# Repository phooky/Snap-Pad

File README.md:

Snap-Pad provides an easy, somewhat safe two party one time pad capability.

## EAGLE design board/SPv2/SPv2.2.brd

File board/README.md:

These are the Eagle CAD board files and libraries for the Snap-Pad.
The files in this directory are published under the CERN Open Hardware License.
See the file "cern_ohl_v_1_2.txt" in the parent directory for more information.

The libraries are in the "lbr" directory; the schematics and boards are in the "Snap-Pad" directory.

SP.sch is the schematic for one-half of a Snap-Pad.
SP.brd is the board file for one-half of a Snap-Pad.
SP-twin.brd is the full board file for the twinned Snap-Pad. There is no associated
  schematic; forward/back annotation is severed and the components are cloned to
  avoid any messiness with part naming. It's a symmetrical board.

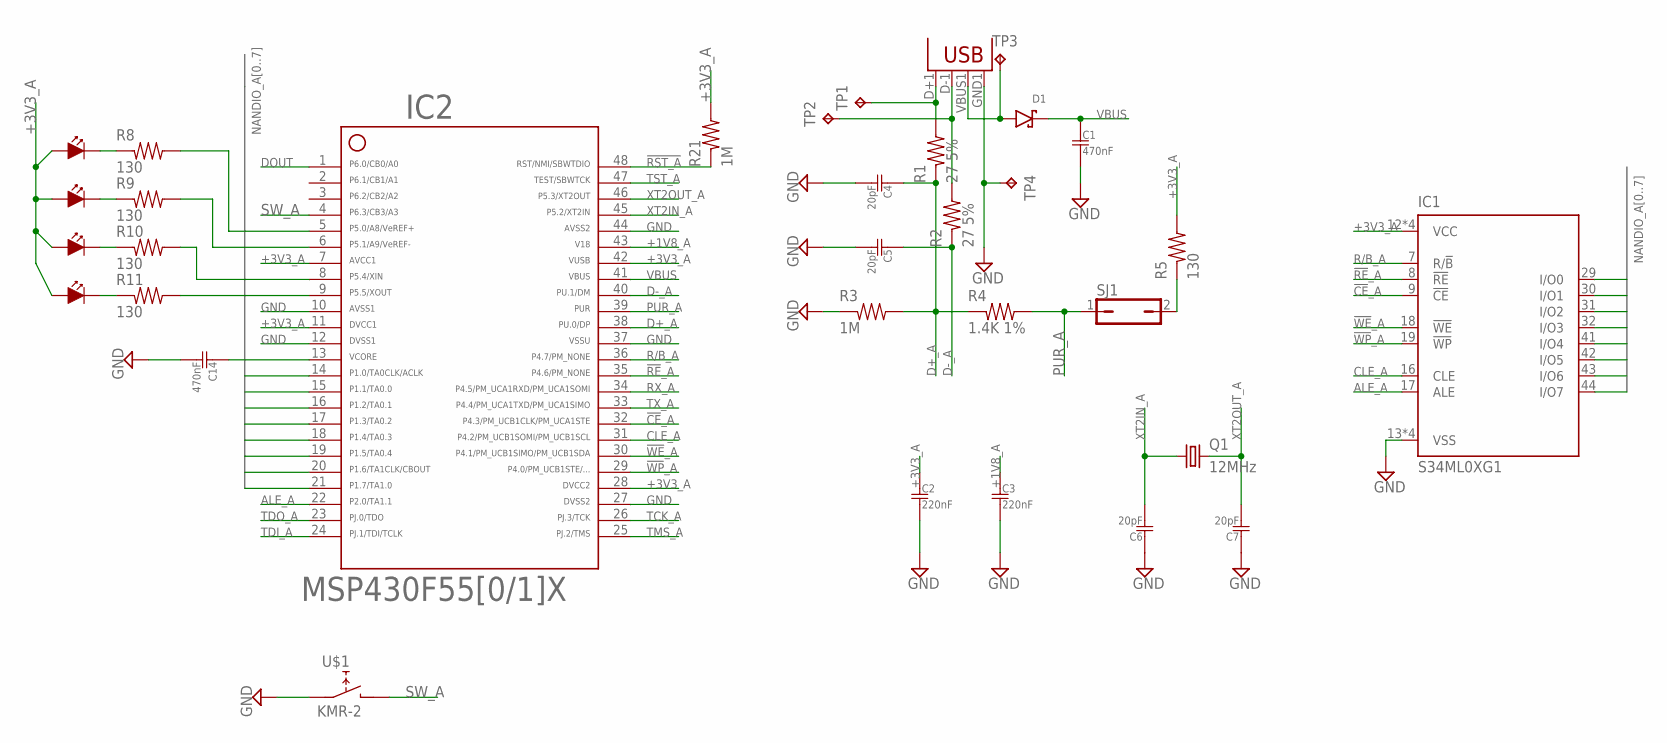
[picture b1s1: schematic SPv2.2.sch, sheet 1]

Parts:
C1, C14: 470nF; R0805
C2, C3: 220nF; R0805
C4, C5, C6, C7: 20pF; R0805
D1: D-SCHOTTKY; SOD123
IC1: S34ML0XG1; TSOP48
IC2: F5508; PT48
JP1: USBA-SMD-MALE; USB-A-SMT-MALE
Q1: 12MHz; CSM-3X
R1, R2: 27 5%; R0805
R3, R21: 1M; R0805
R4: 1.4K 1%; R0805
R5, R8, R9, R10, R11: 130; R0805
SJ1: JP1Q; JP1
TP1, TP2, TP3, TP4: TPTP13R; TP13R
U$1: KMR-2; KMR-2-SWITCH
U$5, U$6, U$7, U$8: LED; LED0805

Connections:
!CE!_A: IC1.9 (!CE), IC2.32
!RE!_A: IC1.8 (!RE), IC2.35
!RST_A!: IC2.48, R21.P$1 (1)
!WE!_A: IC1.18 (!WE), IC2.30
!WP!_A: IC1.19 (!WP), IC2.29
+1V8_A: C3.P$1 (1), IC2.43
+3V3_A: C2.P$1 (1), IC1.12 (VCC), IC1.34 (VCC), IC1.37 (VCC), IC1.39 (VCC), IC2.7, IC2.11, IC2.28, IC2.42, R5.P$2 (2), R21.P$2 (2), U$5.ANODE, U$6.ANODE, U$7.ANODE, U$8.ANODE
ALE_A: IC1.17 (ALE), IC2.22
CLE_A: IC1.16 (CLE), IC2.31
D+_A: C4.P$1 (1), IC2.38, R1.P$1 (1), R3.P$2 (2), R4.P$1 (1)
D-_A: C5.P$1 (1), IC2.40, R2.P$1 (1)
DOUT: IC2.1; also elsewhere on the board
GND: C1.P$2 (2), C2.P$2 (2), C3.P$2 (2), C4.P$2 (2), C5.P$2 (2), C6.P$1 (1), C7.P$1 (1), C14.P$2 (2), IC1.13 (VSS), IC1.25 (VSS), IC1.36 (VSS), IC1.48 (VSS), IC2.10, IC2.12, IC2.27, IC2.37, IC2.44, JP1.GND1 (GND), R3.P$1 (1), TP4.TP, U$1.PA1 (A1), U$1.PA2 (A1); also elsewhere on the board
unnamed: JP1.D+1 (D+), R1.P$2 (2), TP1.TP
unnamed: JP1.D-1 (D-), R2.P$2 (2), TP2.TP
unnamed: C14.P$1 (1), IC2.13
unnamed: R5.P$1 (1), SJ1.2
unnamed: IC2.9, R11.P$2 (2)
unnamed: R10.P$1 (1), U$7.CATHODE
unnamed: R9.P$1 (1), U$6.CATHODE
unnamed: R8.P$1 (1), U$5.CATHODE
unnamed: R11.P$1 (1), U$8.CATHODE
unnamed: IC2.8, R10.P$2 (2)
unnamed: IC2.6, R9.P$2 (2)
unnamed: IC2.5, R8.P$2 (2)
unnamed: D1.ANODE, JP1.VBUS1 (VBUS), TP3.TP
NANDIO_A0: IC1.29 (I/O0), IC2.14
NANDIO_A1: IC1.30 (I/O1), IC2.15
NANDIO_A2: IC1.31 (I/O2), IC2.16
NANDIO_A3: IC1.32 (I/O3), IC2.17
NANDIO_A4: IC1.41 (I/O4), IC2.18
NANDIO_A5: IC1.42 (I/O5), IC2.19
NANDIO_A6: IC1.43 (I/O6), IC2.20
NANDIO_A7: IC1.44 (I/O7), IC2.21
PUR_A: IC2.39, R4.P$2 (2), SJ1.1
R/B_A: IC1.7 (R/!B), IC2.36
RX_A: IC2.34; also elsewhere on the board
SW_A: IC2.4, U$1.PB1 (B), U$1.PB2 (B)
TCK_A: IC2.26
TDI_A: IC2.24
TDO_A: IC2.23
TMS_A: IC2.25
TST_A: IC2.47
TX_A: IC2.33; also elsewhere on the board
VBUS: C1.P$1 (1), D1.CATHODE, IC2.41; also elsewhere on the board
XT2IN_A: C6.P$2 (2), IC2.45, Q1.P$1 (1)
XT2OUT_A: C7.P$2 (2), IC2.46, Q1.P$2 (2)

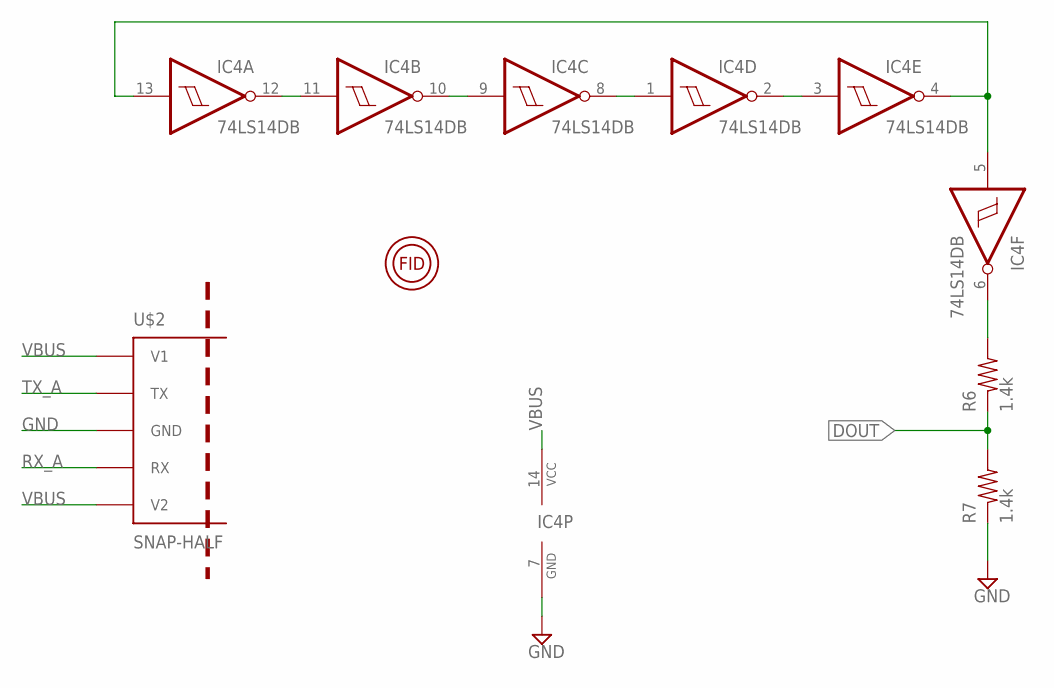
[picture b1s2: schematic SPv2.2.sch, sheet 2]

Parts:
IC4: 74LS14DB; SSOP14
R6, R7: 1.4k; R0805
U$2: SNAP-HALF
U$3: FIDUCAL

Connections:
DOUT: R6.P$1 (1), R7.P$2 (2); also elsewhere on the board
GND: IC4.7 (GND), R7.P$1 (1), U$2.P$3 (GND); also elsewhere on the board
unnamed: IC4.11 (I), IC4.12 (O)
unnamed: IC4.9 (I), IC4.10 (O)
unnamed: IC4.1 (I), IC4.8 (O)
unnamed: IC4.2 (O), IC4.3 (I)
unnamed: IC4.4 (O), IC4.5 (I), IC4.13 (I)
unnamed: IC4.6 (O), R6.P$2 (2)
RX_A: U$2.P$4 (RX); also elsewhere on the board
TX_A: U$2.P$2 (TX); also elsewhere on the board
VBUS: IC4.14 (VCC), U$2.P$1 (V1), U$2.P$5 (V2); also elsewhere on the board

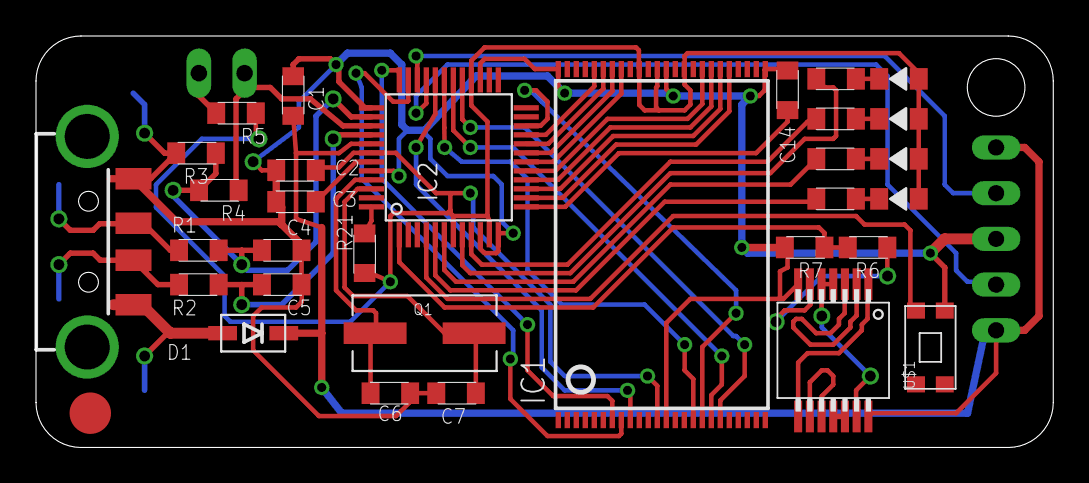
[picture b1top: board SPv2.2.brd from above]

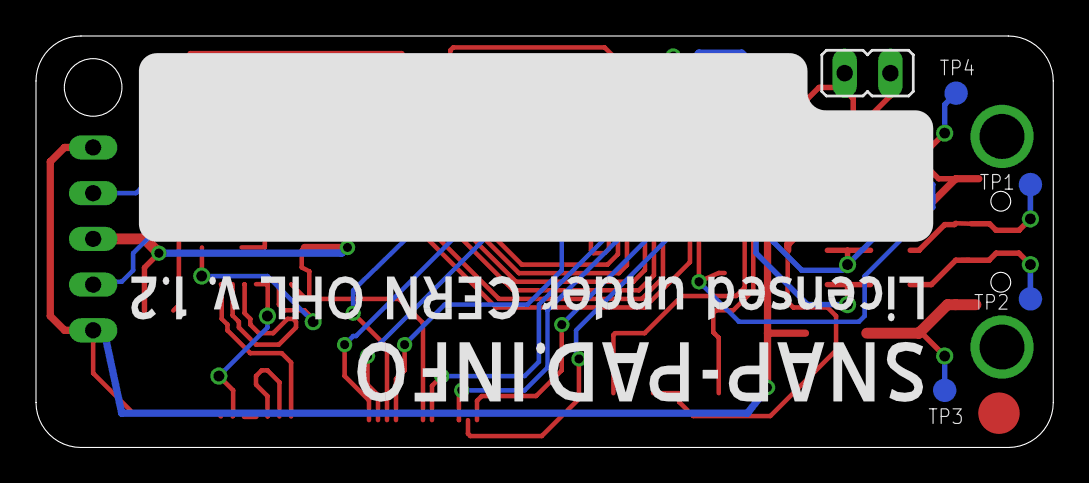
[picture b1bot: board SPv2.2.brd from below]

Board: 2 copper layers, 56.5 x 22.9 mm, 38 parts (6 on the bottom side), 48 nets.

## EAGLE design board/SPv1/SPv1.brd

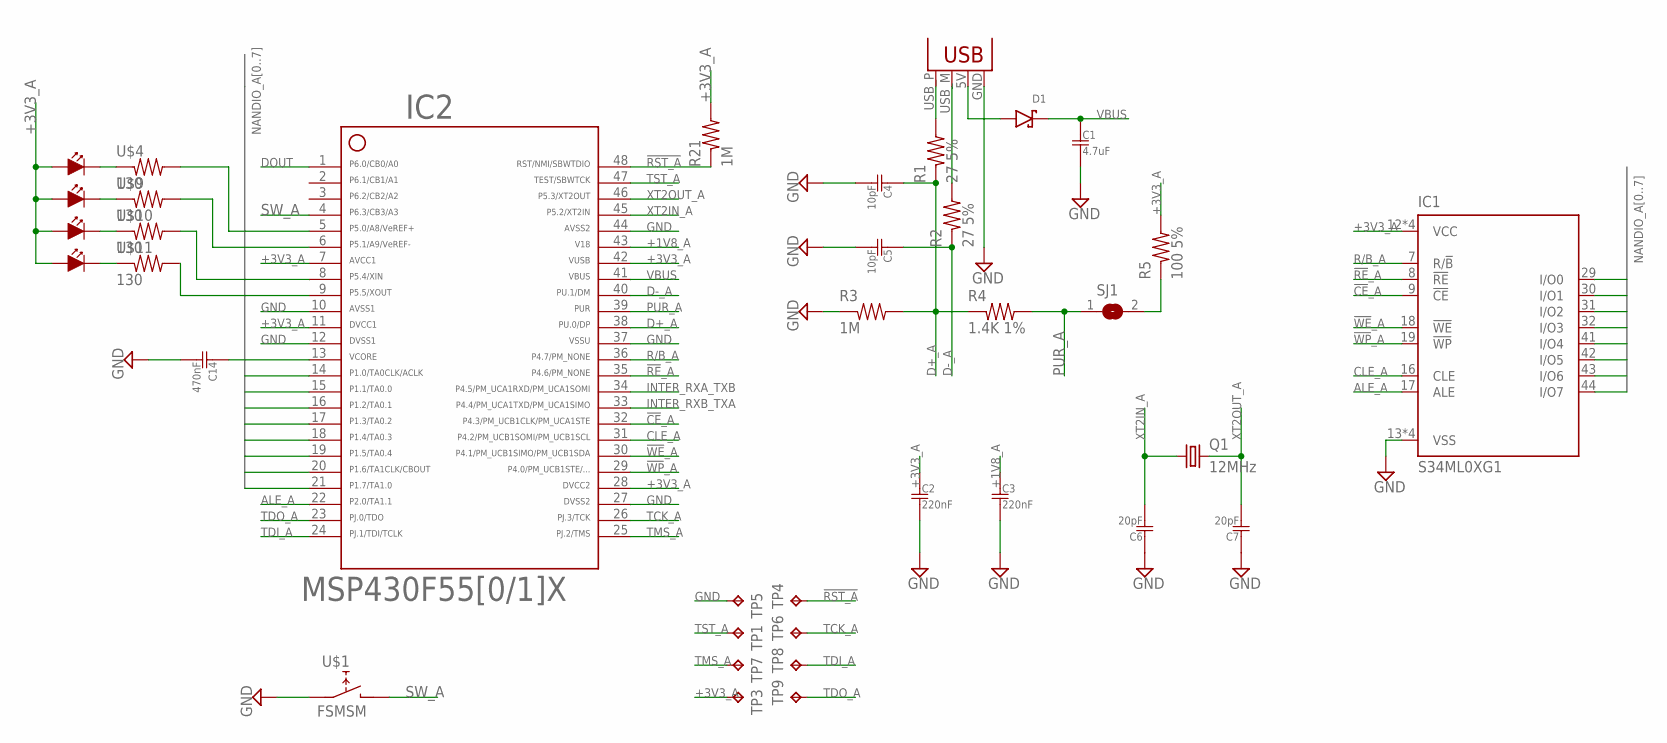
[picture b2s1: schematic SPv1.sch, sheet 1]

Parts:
C1: 4.7uF; R0805
C2, C3: 220nF; R0805
C4, C5: 10pF; R0805
C6, C7: 20pF; R0805
C14: 470nF; R0805
D1: D-SCHOTTKY; SOD123
IC1: S34ML0XG1; TSOP48
IC2: F55[0/1]X---PT48; PT48
JP1: USBPCB; USB-A-PCB
Q1: 12MHz; CSM-3X
R1, R2: 27 5%; R0805
R3, R21: 1M; R0805
R4: 1.4K 1%; R0805
R5: 100 5%; R0805
SJ1: SJW
TP1, TP3, TP4, TP5, TP6, TP7, TP8, TP9: TPTP08SQ; TP08SQ
U$1: FSMSM
U$4, U$9, U$10, U$11: 130; R0805
U$5, U$6, U$7, U$8: LED; LED0805

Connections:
!CE!_A: IC1.9 (!CE), IC2.32
!RE!_A: IC1.8 (!RE), IC2.35
!RST_A!: IC2.48, R21.P$1 (1), TP4.TP
!WE!_A: IC1.18 (!WE), IC2.30
!WP!_A: IC1.19 (!WP), IC2.29
+1V8_A: C3.P$1 (1), IC2.43
+3V3_A: C2.P$1 (1), IC1.12 (VCC), IC1.34 (VCC), IC1.37 (VCC), IC1.39 (VCC), IC2.7, IC2.11, IC2.28, IC2.42, R5.P$2 (2), R21.P$2 (2), TP3.TP, U$5.ANODE, U$6.ANODE, U$7.ANODE, U$8.ANODE
ALE_A: IC1.17 (ALE), IC2.22
CLE_A: IC1.16 (CLE), IC2.31
D+_A: C4.P$1 (1), IC2.38, R1.P$1 (1), R3.P$2 (2), R4.P$1 (1)
D-_A: C5.P$1 (1), IC2.40, R2.P$1 (1)
DOUT: IC2.1; also elsewhere on the board
GND: C1.P$2 (2), C2.P$2 (2), C3.P$2 (2), C4.P$2 (2), C5.P$2 (2), C6.P$1 (1), C7.P$1 (1), C14.P$2 (2), IC1.13 (VSS), IC1.25 (VSS), IC1.36 (VSS), IC1.48 (VSS), IC2.10, IC2.12, IC2.27, IC2.37, IC2.44, JP1.GND, R3.P$1 (1), TP5.TP, U$1.P$1 (A1); also elsewhere on the board
INTER_RXA_TXB: IC2.34; also elsewhere on the board
INTER_RXB_TXA: IC2.33; also elsewhere on the board
unnamed: JP1.USB_P (D+), R1.P$2 (2)
unnamed: JP1.USB_M (D-), R2.P$2 (2)
unnamed: C14.P$1 (1), IC2.13
unnamed: R5.P$1 (1), SJ1.2
unnamed: IC2.9, U$11.P$2 (2)
unnamed: U$7.CATHODE, U$10.P$1 (1)
unnamed: U$6.CATHODE, U$9.P$1 (1)
unnamed: U$4.P$1 (1), U$5.CATHODE
unnamed: U$8.CATHODE, U$11.P$1 (1)
unnamed: IC2.8, U$10.P$2 (2)
unnamed: IC2.6, U$9.P$2 (2)
unnamed: IC2.5, U$4.P$2 (2)
unnamed: D1.ANODE, JP1.5V (VBUS)
NANDIO_A0: IC1.29 (I/O0), IC2.14
NANDIO_A1: IC1.30 (I/O1), IC2.15
NANDIO_A2: IC1.31 (I/O2), IC2.16
NANDIO_A3: IC1.32 (I/O3), IC2.17
NANDIO_A4: IC1.41 (I/O4), IC2.18
NANDIO_A5: IC1.42 (I/O5), IC2.19
NANDIO_A6: IC1.43 (I/O6), IC2.20
NANDIO_A7: IC1.44 (I/O7), IC2.21
PUR_A: IC2.39, R4.P$2 (2), SJ1.1
R/B_A: IC1.7 (R/!B), IC2.36
SW_A: IC2.4, U$1.P$2 (B)
TCK_A: IC2.26, TP6.TP
TDI_A: IC2.24, TP8.TP
TDO_A: IC2.23, TP9.TP
TMS_A: IC2.25, TP7.TP
TST_A: IC2.47, TP1.TP
VBUS: C1.P$1 (1), D1.CATHODE, IC2.41; also elsewhere on the board
XT2IN_A: C6.P$2 (2), IC2.45, Q1.P$1 (1)
XT2OUT_A: C7.P$2 (2), IC2.46, Q1.P$2 (2)

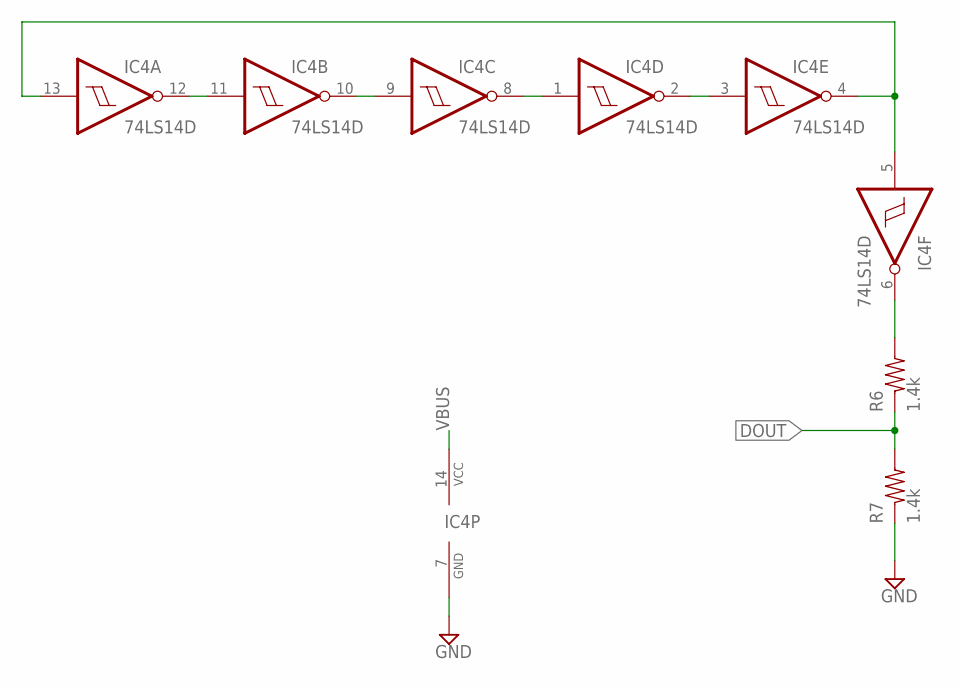
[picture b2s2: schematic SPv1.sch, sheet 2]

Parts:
IC4: 74LS14D; SO14
R6, R7: 1.4k; R0805

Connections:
DOUT: R6.P$1 (1), R7.P$2 (2); also elsewhere on the board
GND: IC4.7 (GND), R7.P$1 (1); also elsewhere on the board
unnamed: IC4.11 (I), IC4.12 (O)
unnamed: IC4.9 (I), IC4.10 (O)
unnamed: IC4.1 (I), IC4.8 (O)
unnamed: IC4.2 (O), IC4.3 (I)
unnamed: IC4.4 (O), IC4.5 (I), IC4.13 (I)
unnamed: IC4.6 (O), R6.P$2 (2)
VBUS: IC4.14 (VCC); also elsewhere on the board

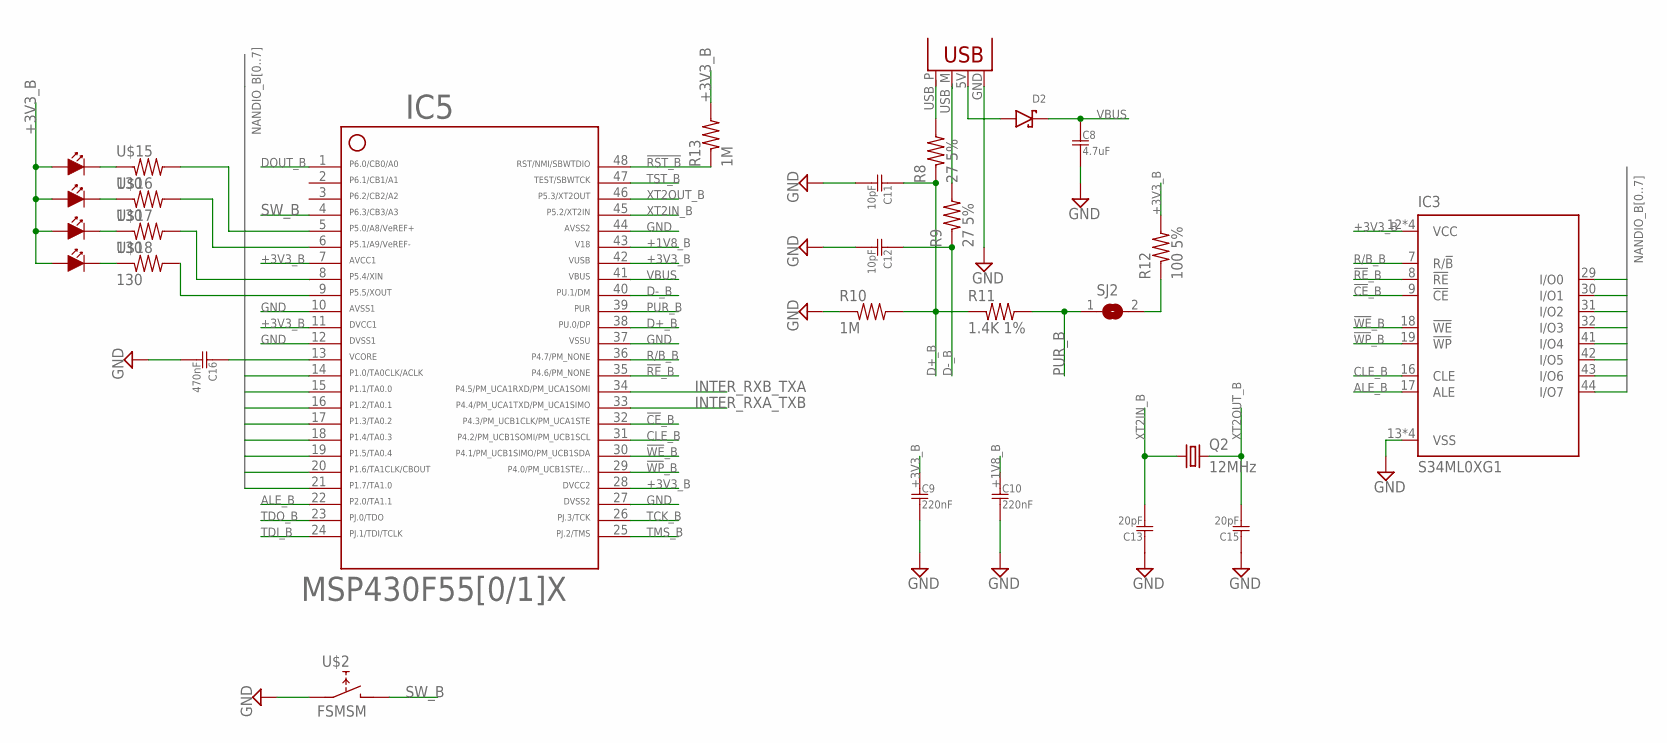
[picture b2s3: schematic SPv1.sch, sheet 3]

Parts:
C8: 4.7uF; R0805
C9, C10: 220nF; R0805
C11, C12: 10pF; R0805
C13, C15: 20pF; R0805
C16: 470nF; R0805
D2: D-SCHOTTKY; SOD123
IC3: S34ML0XG1; TSOP48
IC5: F55[0/1]X---PT48; PT48
JP2: USBPCB; USB-A-PCB
Q2: 12MHz; CSM-3X
R8, R9: 27 5%; R0805
R10, R13: 1M; R0805
R11: 1.4K 1%; R0805
R12: 100 5%; R0805
SJ2: SJW
U$2: FSMSM
U$3, U$12, U$13, U$14: LED; LED0805
U$15, U$16, U$17, U$18: 130; R0805

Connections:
!CE!_B: IC3.9 (!CE), IC5.32
!RE!_B: IC3.8 (!RE), IC5.35
!RST_B!: IC5.48, R13.P$1 (1)
!WE!_B: IC3.18 (!WE), IC5.30
!WP!_B: IC3.19 (!WP), IC5.29
+1V8_B: C10.P$1 (1), IC5.43
+3V3_B: C9.P$1 (1), IC3.12 (VCC), IC3.34 (VCC), IC3.37 (VCC), IC3.39 (VCC), IC5.7, IC5.11, IC5.28, IC5.42, R12.P$2 (2), R13.P$2 (2), U$3.ANODE, U$12.ANODE, U$13.ANODE, U$14.ANODE
ALE_B: IC3.17 (ALE), IC5.22
CLE_B: IC3.16 (CLE), IC5.31
D+_B: C11.P$1 (1), IC5.38, R8.P$1 (1), R10.P$2 (2), R11.P$1 (1)
D-_B: C12.P$1 (1), IC5.40, R9.P$1 (1)
DOUT_B: IC5.1; also elsewhere on the board
GND: C8.P$2 (2), C9.P$2 (2), C10.P$2 (2), C11.P$2 (2), C12.P$2 (2), C13.P$1 (1), C15.P$1 (1), C16.P$2 (2), IC3.13 (VSS), IC3.25 (VSS), IC3.36 (VSS), IC3.48 (VSS), IC5.10, IC5.12, IC5.27, IC5.37, IC5.44, JP2.GND, R10.P$1 (1), U$2.P$1 (A1); also elsewhere on the board
INTER_RXA_TXB: IC5.33; also elsewhere on the board
INTER_RXB_TXA: IC5.34; also elsewhere on the board
unnamed: JP2.USB_P (D+), R8.P$2 (2)
unnamed: JP2.USB_M (D-), R9.P$2 (2)
unnamed: C16.P$1 (1), IC5.13
unnamed: U$13.CATHODE, U$17.P$1 (1)
unnamed: U$12.CATHODE, U$16.P$1 (1)
unnamed: U$3.CATHODE, U$15.P$1 (1)
unnamed: U$14.CATHODE, U$18.P$1 (1)
unnamed: IC5.9, U$18.P$2 (2)
unnamed: IC5.8, U$17.P$2 (2)
unnamed: IC5.6, U$16.P$2 (2)
unnamed: IC5.5, U$15.P$2 (2)
unnamed: R12.P$1 (1), SJ2.2
unnamed: D2.ANODE, JP2.5V (VBUS)
NANDIO_A8: IC3.29 (I/O0), IC5.14
NANDIO_A9: IC3.30 (I/O1), IC5.15
NANDIO_A10: IC3.31 (I/O2), IC5.16
NANDIO_A11: IC3.32 (I/O3), IC5.17
NANDIO_A12: IC3.41 (I/O4), IC5.18
NANDIO_A13: IC3.42 (I/O5), IC5.19
NANDIO_A14: IC3.43 (I/O6), IC5.20
NANDIO_A15: IC3.44 (I/O7), IC5.21
PUR_B: IC5.39, R11.P$2 (2), SJ2.1
R/B_B: IC3.7 (R/!B), IC5.36
SW_B: IC5.4, U$2.P$2 (B)
TCK_B: IC5.26
TDI_B: IC5.24
TDO_B: IC5.23
TMS_B: IC5.25
TST_B: IC5.47
VBUS: C8.P$1 (1), D2.CATHODE, IC5.41; also elsewhere on the board
XT2IN_B: C13.P$2 (2), IC5.45, Q2.P$1 (1)
XT2OUT_B: C15.P$2 (2), IC5.46, Q2.P$2 (2)

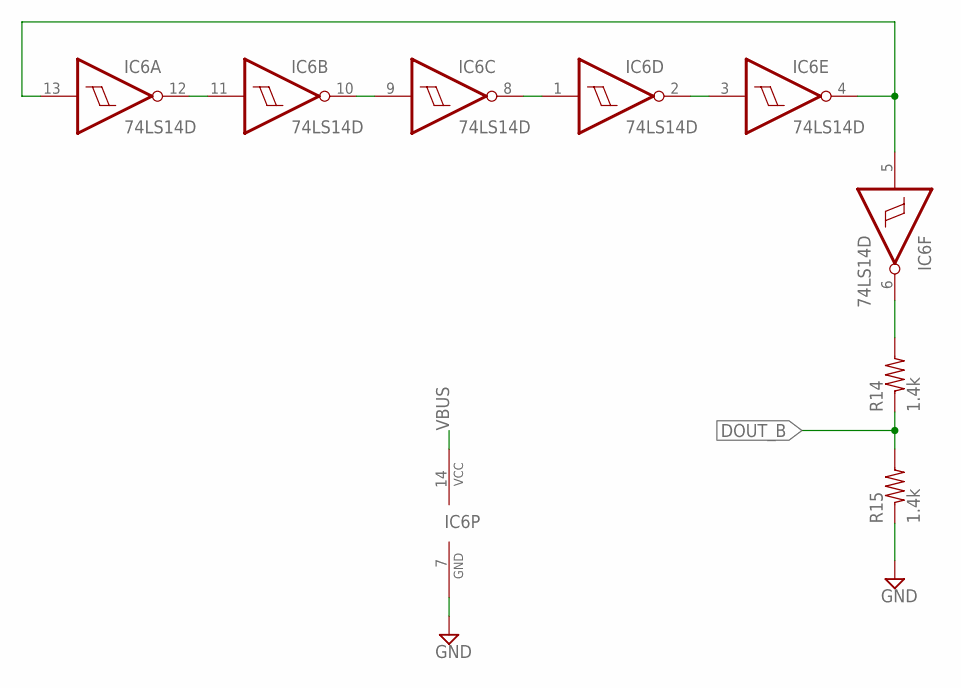
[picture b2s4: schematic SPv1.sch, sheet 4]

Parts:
IC6: 74LS14D; SO14
R14, R15: 1.4k; R0805

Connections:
DOUT_B: R14.P$1 (1), R15.P$2 (2); also elsewhere on the board
GND: IC6.7 (GND), R15.P$1 (1); also elsewhere on the board
unnamed: IC6.11 (I), IC6.12 (O)
unnamed: IC6.9 (I), IC6.10 (O)
unnamed: IC6.1 (I), IC6.8 (O)
unnamed: IC6.2 (O), IC6.3 (I)
unnamed: IC6.4 (O), IC6.5 (I), IC6.13 (I)
unnamed: IC6.6 (O), R14.P$2 (2)
VBUS: IC6.14 (VCC); also elsewhere on the board

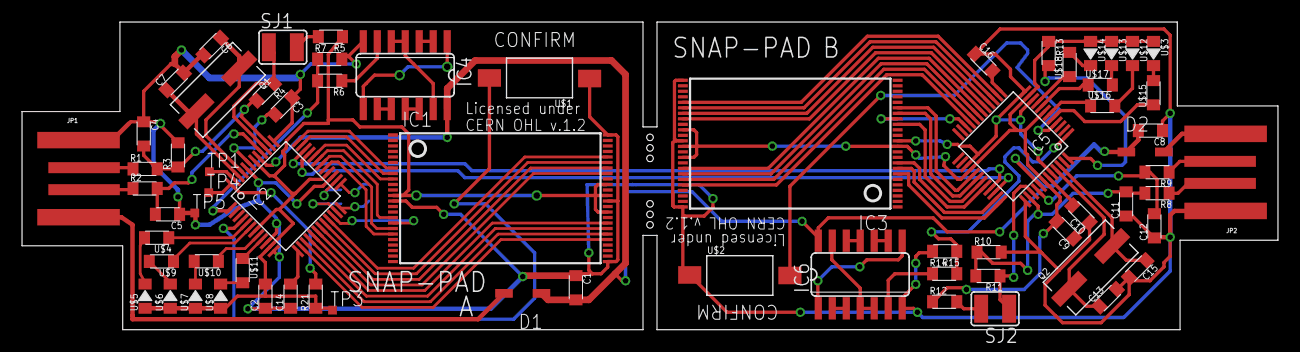
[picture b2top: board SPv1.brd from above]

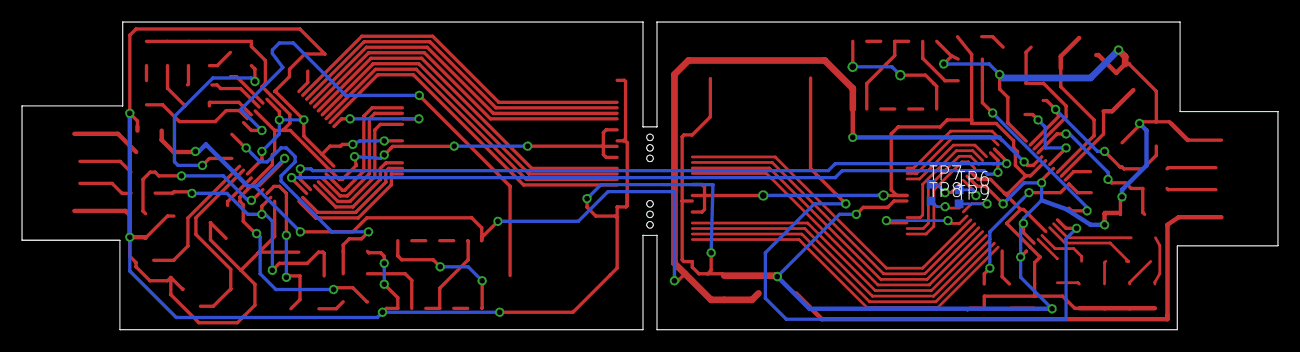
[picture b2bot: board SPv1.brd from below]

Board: 2 copper layers, 114.0 x 27.9 mm, 72 parts (4 on the bottom side), 97 nets.

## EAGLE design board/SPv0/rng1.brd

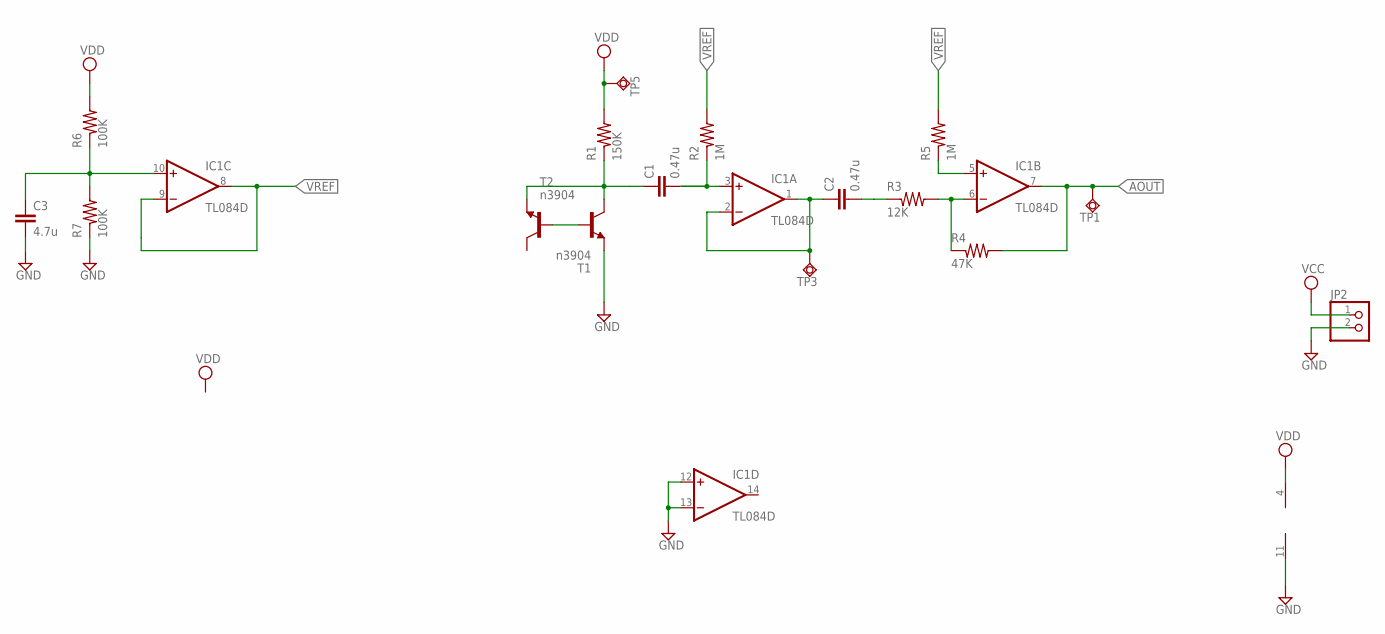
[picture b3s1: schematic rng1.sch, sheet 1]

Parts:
C1, C2: 0.47u; C0805
C3: 4.7u; C0805
IC1: TL084D; SO14
JP2: PINHD-1X2; 1X02
R1: 150K; R0805
R2, R5: 1M; R0805
R3: 12K; R0805
R4: 47K; R0805
R6, R7: 100K; R0805
T1, T2: n3904; SOT23-BEC
TP1, TP3, TP5: TPSQPAD1-13; P1-13

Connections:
AOUT: IC1.7 (OUT), R4.P$2 (2), TP1.TP
GND: C3.2, IC1.11 (V-), IC1.12 (+IN), IC1.13 (-IN), JP2.2, R7.P$1 (1), T2.E; also elsewhere on the board
unnamed: C1.1, R1.P$1 (1), T1.E, T2.C
unnamed: C3.1, IC1.10 (+IN), R6.P$1 (1), R7.P$2 (2)
unnamed: T1.B, T2.B
unnamed: C1.2, IC1.3 (+IN), R2.P$1 (1)
unnamed: C2.1, IC1.1 (OUT), IC1.2 (-IN), TP3.TP
unnamed: C2.2, R3.P$1 (1)
unnamed: IC1.6 (-IN), R3.P$2 (2), R4.P$1 (1)
unnamed: IC1.5 (+IN), R5.P$1 (1)
VCC: JP2.1; also elsewhere on the board
VDD: IC1.4 (V+), R1.P$2 (2), R6.P$2 (2), TP5.TP; also elsewhere on the board
VREF: IC1.8 (OUT), IC1.9 (-IN), R2.P$2 (2), R5.P$2 (2)

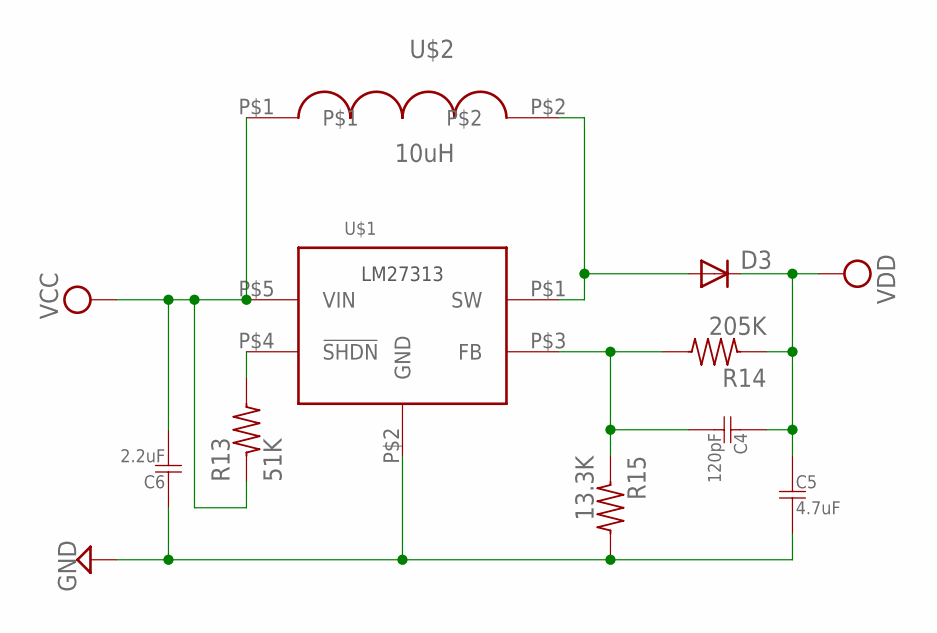
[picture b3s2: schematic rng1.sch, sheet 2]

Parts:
C4: 120pF; R0805
C5: 4.7uF; R0805
C6: 2.2uF; R0805
D3: DIODE-SOD123; SOD123
R13: 51K; R0805
R14: 205K; R0805
R15: 13.3K; R0805
U$1: LM27313; SOT-23-5
U$2: 10uH; L1007

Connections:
GND: C5.P$2 (2), C6.P$1 (1), R15.P$2 (2), U$1.P$2 (GND); also elsewhere on the board
unnamed: R13.P$2 (2), U$1.P$4 (!SHDN!)
unnamed: D3.A, U$1.P$1 (SW), U$2.P$2
unnamed: C4.P$2 (2), R14.P$2 (2), R15.P$1 (1), U$1.P$3 (FB)
VCC: C6.P$2 (2), R13.P$1 (1), U$1.P$5 (VIN), U$2.P$1; also elsewhere on the board
VDD: C4.P$1 (1), C5.P$1 (1), D3.C, R14.P$1 (1); also elsewhere on the board

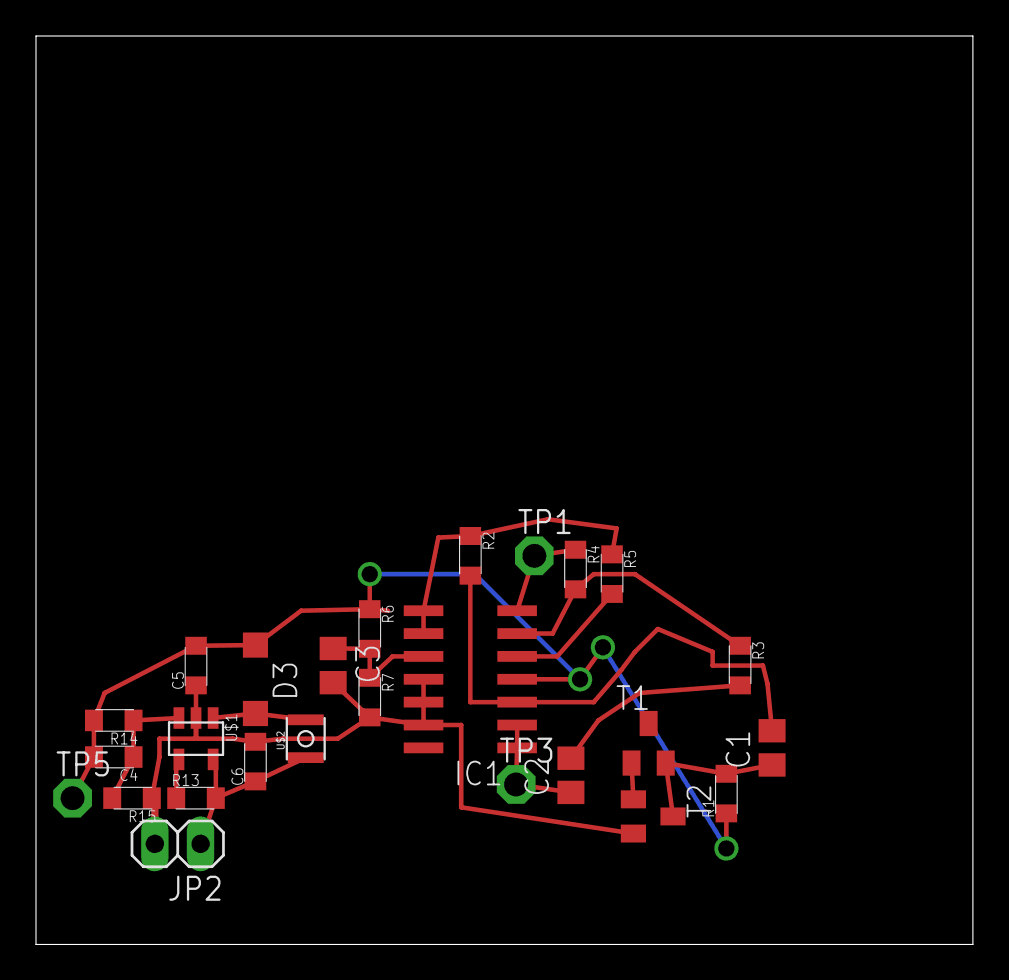
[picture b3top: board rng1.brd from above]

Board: 2 copper layers, 52.0 x 50.5 mm, 26 parts (0 on the bottom side), 16 nets.

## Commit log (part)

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2013-10-26 adding datasheets, flash lib, and schematic start
2013-10-26 adding readme with basic todo and scheduling
2013-10-26 doc for msp430f5508 (x53x was the wrong chip)
2013-10-26 readding hardware user guide
2013-10-26 superceded document
2013-10-27 added uC, xtal, decoupling caps for uC, usb lines/power
2013-10-28 added crystal footprint; added to schematic
2013-10-29 adding RNG ideas
2013-10-29 Added nets and busses for NAND/MSP430 interconnect Designated some pins for RNG
2013-11-23 adding rough circuit for random number generator based on avalanche noise
2013-11-23 reducing to original circuit
2013-11-25 removed obvious ERC problems
2013-11-26 layout of rng in good shape
2013-11-26 pre-autoroute
2013-12-16 fixup usb problems
2013-12-19 adding in descriptors for usb
2013-12-19 adding CCS project for snap-pad v0
2013-12-19 Set most pins to inputs Never stop screaming
2013-12-20 ONFI verified
2013-12-20 rough implementation of raw page read/program
2013-12-21 adding very simple interactivity over cdc
2013-12-23 wait for ready line on reads
2013-12-23 added block erase
2013-12-24 adding documentation
2013-12-24 added own footprints for 0805 parts reorganizing board somewhat
2013-12-26 added LEDs, starting layout
2013-12-26 added schottky diode to library fixed up led symbol swapping in sod123 diode for d1
2013-12-31 fxing up library parts added prototype for read parameter page
2014-01-01 parameter page read command tested
2014-01-01 add doc
2014-01-05 expose raw nand flash read
2014-01-05 adding hooks for experimentation
2014-01-05 pipe XT2 to ACLK pin (should have div 0)
2014-01-06 huh. sending the ACLK signal out on P1.0 makes nand access unreliable. Will have to recheck schematic.
2014-01-06 port already opened by constructor
2014-01-06 adding adc-based hwrng
2014-01-07 adding ADC rng code for shits and giggles
2014-01-07 adding some additional doc
2014-01-08 halfboard v1 done!
2014-01-10 added v1 board with snapping action
2014-01-16 better handling for multiple commands in succession; lib for nand hacking, added some more tests
2014-01-16 adding script for mapping bad blocks
2014-01-18 adding one time pad chip code
2014-01-20 adding header parsing/writing
2014-01-24 fixes to board (connector; PUR line)
2014-01-24 adding extended hamming SEC-DED coding as well as tests
2014-01-24 added CERN OHL notice and moved confirm text to tNames
2014-01-24 add current version of nand code; lint ecc.c
2014-01-24 cleaning up board slightly and prepping for double-sided placement on v2
2014-01-25 toward header initialization
2014-01-26 first pass at header initialization code
2014-01-27 adding main
2014-01-28 close to working initialization; some problem with next_good; writing tons of paragraphs
2014-01-28 header initialization working
2014-01-28 adding switch support
2014-01-28 recognize when SP is not in primary mode.
2014-02-11 adding uart connect check code
2014-02-11 cleaning up warnings adding missing uarts files
2014-02-11 interrupts work better when you have the interrupt enable turned on IT SO HAPPENS
2014-02-12 add some timing fixes to avoid constant jabbering on the line
2014-02-12 improved timing but still need to handle the both-pressed case consistently
2014-02-13 fix "we're both cheating" deadlock issue (when both buttons are pressed)
2014-02-13 uart now uses a ring buffer; cleanup; framework for handling uart commands
2014-02-13 added timer-based led blinking
2014-02-13 saving project settings. small code model ftw.
2014-02-13 hard reset protocol in
2014-02-14 removing is_a (symmetrical now) adding debug compile-time flag
2014-02-14 wrapping up for tonight
2014-02-17 Snap Pad v2, halfsies design, routed
2014-02-17 added alignment holes and silkscreen
2014-02-17 adding twinned board
2014-02-17 silks cleaned up on twin
2014-02-18 Adding license information
2014-02-18 updating .gitignore
2014-02-18 Oops-- datasheets should never have been in repo
2014-02-18 readme was out of date
2014-02-21 Adding cname to serve up snap-pad.info
2014-02-21 subdomain cname
2014-02-22 adding use cases
2014-02-22 formatting change
2014-02-25 simplify led blink patterns, add larson scanner mode
2014-02-26 tweak LEDs; lock both halves after a factory reset
2014-02-27 Eliminating obsolete code
2014-03-03 adding hanging edge connector
2014-03-06 adding in second timer
2014-03-06 add usb detection code
2014-03-07 finally got the timing right: USB end is always master in twinned boards; breaking out code to make the whole shebang a little more readable.
2014-03-08 cleaning up usb commands a bit
2014-03-10 adding remote button ping and wait on button press in twinned master mode
2014-03-10 fix uart (set to 460800 baud)
2014-03-12 added page random fill and test
2014-03-12 modify randread script to pull from paragraph
2014-03-12 added more flexibility to rand read script
2014-03-13 fix for ping value check and transmit buffer bug
2014-03-24 adding buffer management
2014-03-24 fix for missing nand.h def'ns in buffer.c
2014-03-24 shifting over to swappable buffers
2014-03-27 deep breath: randomization mode implemented
2014-03-27 fix RNG generator so as not to step on its own toes
2014-03-27 added debugging code and of course it works now.
2014-03-30 latest stab at pushing blocks over uart
2014-04-03 adding missing hal and hwrng files
2014-04-04 replaced TX ring buffer with immediate buffer write; finally tracked down weirdness with tx interrupt (TXIFG was being used in different ways for byte and buffer writes)
2014-04-07 adding in better read and erase debug commands; removing obsolete maint script
2014-04-11 fix ping failures from too-frequent button pings
2014-04-11 fixing dropped byte problem
2014-04-11 fixing up terrible uart bugs because I am a terrible programmer
2014-04-13 remove block:page:para confirmation on read requests disable remote button ping after the first command on the USB port (seeing some weird behavior)
2014-04-16 drop pings after commands
2014-04-17 added block marking and scanning
2014-04-18 * added super-simple checksum code * duurrrrr maybe chip go faster if clock go faster duurrrrr
2014-04-19 adding checksum and bad block marking to generation step
2014-04-22 adding use block debugging
2014-04-23 adding additional checks (bad blocks kill checksums)
2014-04-24 sorta in-code documentation, a bit of cleanup, getting ready for P/R commands
2014-04-24 adding some base64 code to support R/P
2014-04-24 fix typo/goof
2014-04-24 added tests for base64, fixed error
2014-04-25 added parsing and prototypes for retrieval and provisioning calls
2014-04-25 adding button confirm detection
2014-04-25 bugfix
2014-04-27 retrieve blocks individually but with single confirm
2014-04-27 bugfix: parsing multi-block retrieval
2014-04-28 refactor LED modes
2014-04-28 more led refactor
2014-04-28 better LED status
2014-04-29 fix USB/commit button startup conflict
2014-04-29 pare down debugging functions
2014-04-29 add para search
2014-04-29 added otp_release_para
2014-04-30 bugfix for b64 print function
2014-04-30 buxfix #2 for b64 print
2014-05-02 improved diagnostic reporting
2014-05-02 set acknowledge and ready led states during/after operations
2014-05-03 basic jig for v0.2.1 board
2014-05-05 serial snap pad identification
2014-05-23 added diagnostics to scripts
2014-05-23 adding warning for debug builds added single-mode detection
2014-05-23 added used block check and detection
2014-05-23 retrieval script implemented refactored out redundant para used code
2014-05-23 better para retrieval
2014-05-23 provisioning implemented
2014-05-24 snap-pad detection
2014-06-15 adding TI USB code
2014-06-15 adding driverlib
2014-06-15 partway there, but giving up for now. Will take another stab at this In The Future.
2014-06-16 updated project for CCS6
2014-10-02 updated part sizes and numbering
2014-10-03 v2.2, starting to compress some components
2014-12-02 * some updates for v2.2 of the board (reducing components) * cleaning up error code * verifying R codes do work
2014-12-02 added timeouts and removed inconsistent '\r's. resolves #3.
2014-12-02 clean up print code
2014-12-09 doc update regarding error
2015-02-04 optimization on ECC computation
2015-02-05 Removing dead code from previous optimization
2015-02-06 separate debug and release builds
2015-02-09 better adc bit mixing and more flexible code
2015-02-26 new switch smaller 74ls14 jumper header instead of solder jumper board layout in progress
2015-02-28 rerouting in progress
2015-02-28 test pads in, routing finalized
2015-02-28 next board order done
2015-03-02 finished v2.2, twinned board for fab
2015-03-05 creating factory test firmware. implemented LED test mode. implemented UART ping test mode. implemented version test command.
2015-03-19 adding test script
2015-03-19 updated factory test to deal with corrent buffer size
2015-03-20 shaping up the hrng
2015-03-20 ugh. really a scripting error. drop the "OK" confirmation from the end of the 16B rng dumps.
2015-03-22 refactoring hex into print.h/c adding ONFI read id dump to factory test firmware (extra check for substitute parts)
2015-03-22 adding block write test
2015-03-22 remove leftover print
2015-03-23 added 'R' (random block) command to factory test firmware
2015-03-24 rounded corners on board added new, more interesting silkscreen on back added script for pulling down entire random blocks from factory test firmware
2015-03-24 finalizing half-board, switch testing remains
2015-03-27 added debug dumper
2015-04-09 wrapping up api
2015-04-09 cleaned up and refactored eagle CAD files.
2015-04-09 adding zip of gerbers for v0.2.3 (hopefully last cut before production)
2015-05-01 latest tweaks to testing script
2015-05-02 cleaning up version code adding mock snap-pad and tests to provide script test harness
2015-05-04 tests for mock S-P chugging
2015-05-04 getting python libs in shape
2015-05-04 Changing to PID/VID from http://pid.codes/1209/2400/
2015-05-04 get rid of scripts directory
2015-05-05 more snap pad tests and fixes; some methods made private
2015-05-05 added hwrng and test
2015-05-05 getting rid of old main
2015-05-05 fixing up some imports for python3
2015-05-10 adding module stuff
2015-05-21 creating more verbose and complete configuration file
2015-05-21 moving connection state info to uart.h from config.h
2015-05-21 fixup spaces->tabs for factory_test
2015-05-21 documented all NAND api calls.
2015-05-21 fixup tabs/spaces on uarts.c
2015-05-21 remove references to planes from nand api
2015-05-22 more symbols for numbers
2015-05-24 changed prototypes to 2k page model
2015-05-24 updated implementations of OTP to handle pages
2015-05-24 type fixup
2015-05-25 more obscure error reporting at randomization time fix for nand block checksum introduced in page size changes
2015-05-26 fix debug read update debug dump script
2015-05-28 fixing up debug dumper to get right amount of data
2015-06-04 bring tests up to date with firmware
2015-06-05 updated test to match ideal firmware
2015-06-06 added incremental buffer b64 printing to avoid having four concatenated 512B seperate encodes with zero padding
2015-06-09 fix retrieval index bug
2015-06-09 * avoid unintentional page marking on a buffer * fix sizing error in multiply
2015-06-11 fix buffer initialization
2015-06-13 bringing it together
2015-06-16 getting there on the encoding
2015-06-17 okay actually works now
2015-06-17 armored encrypted data
2015-06-23 clean up and simplify interface ahead of armoring
2015-06-23 padding methods
2015-06-25 moving encoding into containers.py moving more into config file
2015-07-05 adding tests for containers
2015-07-05 replace to_ and from_ascii to the more accurate to_/from_json.
2015-07-05 cleaning up, reducing containers, adding marshalling and unmarshalling
2015-07-05 added padding test for marshalled data
2015-07-06 added to/from ascii armor versions cleaned up to_ and from_ methods wth helpers
2015-07-06 added ascii test
2015-07-06 ensure that ascii works
2015-07-11 adding console scripts, setup
2015-07-15 starting in on top-level script
2015-07-17 Update hwrng interface to correctly return 64B of data. Adding random and list commands to script and cleaning up parser.
2015-07-21 moved helper fn encode implemented in main.py
2015-07-22 round trip with the mock hw
2015-07-23 turns out that darwin works the same way

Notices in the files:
board/SPv1/SPv1.brd:
Licensed under
CERN OHL v.1.2
parts and their libraries:
SparkFun-Connectors: Licensing: CC v3.0 Share-Alike You are welcome to use this library for commercial purposes.
